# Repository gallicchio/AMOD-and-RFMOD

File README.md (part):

# AMOD and RF-MOD: boards of analog and RF building blocks

Nine 100 x 100 mm boards of "tiles" for an FPGA with fast converters: seven first-level boards (for the ECP5-2ADC-2DAC
board, or an Icepi Zero with its AD9280/AD9708 module), among them AMOD-N, as simple as the first, the conversion board
AMOD-C and two motor boards, AMOD-M (brushed motors and actuators) and AMOD-B (a brushless gimbal motor), and two
second-level boards built around the ECP5-2ADC-2DAC board's two DACs and two ADCs: PhMOD (AMOD-2 until Prompt 17) and
IQ-MOD.  Each tile is one circuit with its own SMA jacks: cable a DAC to its input and its
output to an ADC, and compare the measurement with the expected result printed beside it.  The silkscreen draws every
tile's wiring as it is laid in copper.  The tutorial they serve is `icepi-zero-dac-adc/tutorial/`, whose Appendix D
specified them.

Rev A, 2026-10-25 (AMOD-N, AMOD-C, AMOD-M and AMOD-B added 2026-10-28).  Designed by Claude with Jason Gallicchio, not yet ordered.

| board | what | tiles | layers | parts per board |
|---|---|---|---|---|
| [AMOD-P](docs/HANDBOOK_amod_p.md) | passive: pads, RC and LC filters, resonators, a crystal, a clipper, a delay line, LEDs, an AM loopstick | 13 | 2 | $17.07 |
| [AMOD-N](docs/HANDBOOK_amod_n.md) | the second passive board: calibration standards, two splitters, a quarter-wave stub, a low-pass, a diode detector, a bias-T, a 1:1 balun and a 1:4 transformer; a step attenuator (by hand or the FPGA) and an oscillator on the Pmod's 3.3 V | 11 | 4 | $43.91 |
| [AMOD-A](docs/HANDBOOK_amod_a.md) | active on USB-C: gain blocks, an HF LNA, an HB100 Doppler radar, a one-pin ADC, a 4046 PLL, heat, a mixer, impedance and I-V, ultrasound, audio | 12 | 4 | $49.73 |
| [AMOD-C](docs/HANDBOOK_amod_c.md) | conversion: two regulators and an electronic load, a charge pump, switched capacitors (a filter, a resistor), a delta-sigma modulator, a track-and-hold, a SAR comparator, a differential pair, a cascode, a V-to-F, a precision rectifier | 12 | 4 | $43.93 |
| [AMOD-M](docs/HANDBOOK_amod_m.md) | motors on a 5-16 V supply: a DC motor with its encoder, a stepper, a servo, a solenoid's flyback three ways, a DC-coupled bridge amplifier, a buck power stage, and a hall, an optical and a load-cell sensor for their loops | 11 | 4 | $36.49 |
| [AMOD-B](docs/HANDBOOK_amod_b.md) | a brushless gimbal motor on a 5-12 V supply: a three-phase driver from the FPGA, the motor over a magnetic encoder, two halls and an index sensor, its back-EMF, its phase and bus currents, its vibration, and an IMU | 12 | 4 | $42.45 |
| [RF-MOD](docs/HANDBOOK_rf_mod.md) | 915 MHz and 2.4 GHz: a diode-ring mixer, two filters, a QPL9547 LNA, a gain block, two ADL5350 mixers, a synthesizer with two outputs, a TRF3722 I/Q transmitter, power and a 25 MHz reference | 10 | 4 | $66.51 |
| [PhMOD](docs/HANDBOOK_phmod.md) | physics at HF, magnetic resonance, the ionosphere and light: a 1 W pulse amplifier and duplexer, a two-channel HF receiver, a VLF loop amplifier, a reflection bridge, coupled resonators, a coil driver, a noise source, a laser driver with an RF bias-T | 10 | 4 | $77.89 |
| [IQ-MOD](docs/HANDBOOK_iq_mod.md) | coherent I/Q and microwave physics, 0.4-6 GHz: an I/Q modulator and demodulator on one synthesizer's two outputs, a dual directional coupler, an LNA, a log detector, a switch, a noise source, GNSS, an ODMR loop | 11 | 4 | $99.71 |
| [Icepi adapter](icepi_adapter/README.md) | the tutorial's 2x12 Icepi Zero adapter with a Pmod socket | | 4 | hand-soldered |

Each tile's name and what it does are printed on the board: the jacks' names sit on their own tile's frame beside each
jack, a tile's title in words on its top frame where it fits, its ranges and levels inside it.  Ports are named in
capitals (IN, OUT, LO), tiles in mixed case (Step attenuator, Diode mixer), everything else in lower case.  Turn a board
over and each tile has a panel on the back under it: its limits, its loads, its supply, and where there is room a small
plot of the response to expect, so the board can be cabled without the handbook open.  Below, each board's
picture and a table of its tiles, each row a summary of the tile's entry in the board's handbook (linked from the tile's
number), where the tile has its own picture, what to expect, the circuit and its parts.  What to buy beside the boards,
with links and prices, is in [docs/KIT.md](docs/KIT.md).

## The boards

<!-- board:amod_p -->
### [AMOD-P](docs/HANDBOOK_amod_p.md): the passive board

| tile | what it does | chip | specs | limits | experiments | how to use it | you need |
|---|---|---|---|---|---|---|---|
| [**p1**](docs/HANDBOOK_amod_p.md#p1) pi pad | Divides the voltage by 10 (-20 dB) and looks like 50 ohm from both ports. | passive | 61.9 / 249 / 61.9 ohm pi; -20.0 dB; DC to well past 30 MHz. | -20 dB only between 50 ohm on both sides (-14 dB into a high impedance); about 0.1 W (+-3 V) at IN. | A known weak signal for a receiver or LNA; padding a mismatched cable; checking the ADC's 50 ohm setting. | DAC to IN, OUT to the ADC set to 50 ohm. | Nothing beyond SMA cables. |
| [**p2**](docs/HANDBOOK_amod_p.md#p2) RC low-pass | A first-order RC low-pass: passes below 159 kHz and falls 20 dB per decade above. | passive | 1 k and 1 nF; -3 dB at 159 kHz; time constant 1 us. | OUT is a 1 k source: read it on the ADC's high-impedance setting (50 ohm divides it by 21). | A Bode plot, 45 degrees at the corner, the step response, the lag plant for feedback control. | DAC to IN, OUT to the ADC on high impedance; sweep the frequency or send a step. | Nothing beyond SMA cables. |
| [**p3**](docs/HANDBOOK_amod_p.md#p3) RC high-pass | A first-order RC high-pass, the mirror image of p2. | passive | 1 nF and 1 k; -3 dB at 159 kHz; +20 dB per decade below. | OUT is a 1 k source: read it on high impedance. | A Bode plot, AC coupling, a differentiator (a step gives a 1 us spike). | DAC to IN, OUT to the ADC on high impedance. | Nothing beyond SMA cables. |
| [**p4**](docs/HANDBOOK_amod_p.md#p4) series RLC | A series 100 uH and 220 pF resonator between 50 ohm ports: a band-pass peak that the DIP switch moves. | passive | 1.07 MHz with both switches off, 0.98 (way 1, +47 pF), 0.89 (way 2, +100 pF), 0.83 (both); Q about 6. | The 50 ohm ports load it: Q is 6, where the coil alone would allow about 60. | Resonance and Q, the phase through resonance, tracking a resonance with a lock-in or a PLL, a resonant plant to control. | Sweep the DAC into IN, OUT to the ADC (50 ohm); set the DIP switch. | Nothing beyond SMA cables. |
| [**p5**](docs/HANDBOOK_amod_p.md#p5) LC low-pass | A 5th-order Butterworth LC low-pass at 9 MHz: the anti-alias filter for a 25 MS/s ADC, or the smoothing filter after a DAC. | passive | -3 dB at 8.9 MHz, -30 dB at 18 MHz; 50 ohm in and out. | The response is as designed only with 50 ohm on both ports. | Aliasing with and without it; a filter's magnitude, phase and group delay; cleaning a DAC's staircase. | Between the DAC and its load, or between a signal and the ADC (50 ohm). | Nothing beyond SMA cables. |
| [**p6**](docs/HANDBOOK_amod_p.md#p6) LC low-pass | A 3rd-order LC low-pass near 120 kHz: turns a one-bit (delta-sigma or PWM) stream into a tone. | passive | 10 nF, 150 uH, 10 nF (C0G); -3 dB at 118 kHz; 50 ohm. | Designed for 50 ohm on both ports. | One-bit DAC reconstruction, delta-sigma noise shaping seen at the output, a slow plant for control. | DAC (or a one-bit stream through 50 ohm) to IN, OUT to the ADC. | Nothing beyond SMA cables. |
| [**p7**](docs/HANDBOOK_amod_p.md#p7) band-pass | A 3rd-order LC band-pass, 4.7-7.5 MHz: the band round the tutorial's 6.25 MHz digital-communications carrier. | passive | Peak at 6.3 MHz, -3 dB from 4.7 to 7.5 MHz; 50 ohm. | Only 3rd order: the skirts fall about 18 dB per octave. | Band-limiting a modem's chips (spread spectrum, LoRa chirps); a transmitter's harmonics removed; a receiver's front end. | In line between the DAC and the ADC, or ahead of a receiver. | Nothing beyond SMA cables. |
| [**p8**](docs/HANDBOOK_amod_p.md#p8) quartz crystal | A 4 MHz quartz crystal in series between the jacks: a very sharp pass at its series resonance and a notch at its parallel resonance about 6 kHz above. | passive | f_s near 4.000 MHz (-3.7 dB); f_p about 6 kHz higher; Q about 50,000 (C_m 15 fF, C_0 4 pF). | Needs frequency steps of a few hertz (the FPGA's NCO); keep the drive under about +-1 V (crystals have a drive-level limit near 100 uW). | Q from the width and from the ring-down; series against parallel resonance; pulling f_p with a capacitor across OUT (an SMA tee); the temperature coefficient. | Sweep the DAC slowly through 4.000 MHz into IN, OUT to the ADC, lock-in detection in the gateware. | An SMA tee and a few capacitors (or open cable stubs) for the pulling experiment. |
| [**p9**](docs/HANDBOOK_amod_p.md#p9) ceramic res. | A 455 kHz ceramic resonator in series: a pass at 455 kHz and a notch a few kHz above; the AM superhet's IF element. | passive | Q of a few hundred: between p4's LC (6) and p8's quartz (50,000). | A two-terminal resonator, not a three-terminal IF filter: one peak, no flat passband. | Q compared across LC, ceramic and quartz; an IF stage for a superhet built in gateware. | Sweep 440-480 kHz into IN, OUT to the ADC. | Nothing beyond SMA cables. |
| [**p10**](docs/HANDBOOK_amod_p.md#p10) clipper | 1 k in series and a 1N4148 diode each way to ground: clips any signal to about +-0.6 V. | passive | Clips at +-0.6 V; a 1 k source. | Read OUT on high impedance; up to +-4 V in (the 1 k holds the diode current to 4 mA). | Harmonics of a clipped sine against amplitude; odd harmonics, and even ones with a DC offset added; distortion. | DAC sine to IN, OUT to the ADC on high impedance, FFT in the gateware or Python. | Nothing beyond SMA cables. |
| [**p11**](docs/HANDBOOK_amod_p.md#p11) delay line | A 400 ns, 50 ohm delay line made of 20 LC sections, with taps every 100 ns: 260 feet of RG-58 on a board. | passive | Z0 51 ohm, 20 ns a section, cut-off 16 MHz, flat to about 10 MHz; taps through 470 ohm. | Disperses near 16 MHz (a chirp spreads); a tap is x1 into a high impedance, /10 into 50 ohm. | Reflections from an open, a short and a matched end; time-domain reflectometry; echoes for an equalizer; a radar target on a cable; a pure-delay plant for control. | A pulse or chirp from the DAC into IN; OUT open, shorted or terminated; the taps and OUT to the ADCs. | An SMA short and a 50 ohm terminator (the kit's ANNE-50+) for the reflection experiments. |
| [**p12**](docs/HANDBOOK_amod_p.md#p12) LEDs | Four LEDs (red, yellow, green, blue) behind 100 ohm, one at a time from the DIP switch: Planck's constant from the voltage where each starts to glow. | passive | 630, 596, 525 and 469 nm (DIP ways 1-4); 100 ohm in series; IN 0-5 V. | The InGaN green and blue sit above the line (their knee is not just hc / e lambda); the colours are not printed, so light them. | Planck's constant; LED I-V curves (with AMOD-A's a10); light against current. | Ramp the DAC (or the host's LED output) into IN and read the LED loop's voltage; one DIP way at a time. | Nothing (a dark room helps). |
| [**p13**](docs/HANDBOOK_amod_p.md#p13) AM loopstick | An AM-band antenna: a ferrite-rod coil screwed into the terminal, tuned by four switched capacitors or an external tuning capacitor on VAR C, its tap on the jack. | passive | With a 330 uH coil: 1.28 MHz (47 pF) down to 0.40 MHz (470 pF), and the sums between; the kit's 240 uH coil tunes about 17 % higher. | The switches tune in 15 steps; continuous tuning needs a capacitor on VAR C (a polyvaricon and its dial are 20 mm square: no room on the tile).  A weak signal that needs a4's gain before the ADC. | Real AM stations; the resonance and Q of a loopstick; the tutorial's AM radio gateware. | Coil ends to GND and HOT, its tap (if it has one) to TAP; rod along the bottom edge with two cable ties; OUT to AMOD-A's a4, a4 to the ADC; the DIP picks the band, or a tuning capacitor on VAR C (frame to GND) tunes within it. | An AM loopstick coil and two cable ties (kit: Atomic-29 240 uH loopstick, Panduit PLT1M-C); optionally a 365 pF tuning capacitor with a knob (kit: Amplified Parts single-section 365 pF). |

More on each tile, with its picture, in the [AMOD-P handbook](docs/HANDBOOK_amod_p.md); what to buy in [KIT.md](docs/KIT.md).

<!-- /board:amod_p -->

<!-- board:amod_n -->
### [AMOD-N](docs/HANDBOOK_amod_n.md): the second passive board

| tile | what it does | chip | specs | limits | experiments | how to use it | you need |
|---|---|---|---|---|---|---|---|
| [**n1**](docs/HANDBOOK_amod_n.md#n1) calibration | Calibration standards for a network analyzer, on the board: a short and an open at the jacks' pins, a 50 ohm load, a 25 ohm check standard and a thru. | passive | SHORT: the centre pin poured to ground all round.  OPEN: the bare pin.  LOAD: 2 x 100 ohm at the end of 4 mm of 50 ohm line.  25 OHM: 2 x 49.9 ohm (VSWR 2, \|Gamma\| 1/3, 9.5 dB return loss).  THRU: 19.8 mm of 50 ohm coplanar line, about 115 ps. | The standards are modelled, not measured: the open's fringing (tens of fF) and the short's inductance (tens of pH) count above about 3 GHz, and the 0402 load is a 20 dB return loss at 3 GHz.  Check them once against the NanoVNA's SMA standards. | A full SOLT calibration of IQ-MOD's reflectometer (q1, q2, q5) or of a NanoVNA at the board's surface; the 25 ohm standard as its check; every other tile then measured from its pads with its jacks taken out (they are all the same part). | The analyzer's port to SHORT, OPEN and LOAD in turn; its two ports to THRU A and THRU B for the two-port step; then any tile. | Nothing beyond SMA cables. |
| [**n2**](docs/HANDBOOK_amod_n.md#n2) resistive splitter | A resistive power splitter: three 16.9 ohm in a star, every port 50 ohm, 6 dB from any port to either other, from DC to 6 GHz. | passive | 3 x 16.9 ohm (50 / 3); -6.0 dB each way; DC-6 GHz; OUT 1 and OUT 2 on lines of equal length. | No isolation (OUT 1 to OUT 2 is also -6 dB); 6 dB of loss where a transformer splitter loses 3; about +20 dBm at IN (1/16 W resistors). | One DAC into both ADCs to measure the converters' own gain and skew; the reference and test paths of a scalar network analyzer; its isolation against n3's. | IN from the source; OUT 1 and OUT 2 to two 50 ohm loads.  Symmetric: any port can be IN. | Nothing beyond SMA cables. |
| [**n3**](docs/HANDBOOK_amod_n.md#n3) transformer splitter | A transformer power splitter (and combiner): half the power to each port, 3 dB, with the two ports isolated from each other, 0.5-400 MHz. | [ADP-2-1+](https://www.minicircuits.com/WebStore/dashboard.html?model=ADP-2-1%2B) | 3.1-3.4 dB from SUM to each port; 25-34 dB between port 1 and port 2; 0.5-400 MHz (the datasheet). | A transformer: nothing below 0.5 MHz; the isolation holds only with 50 ohm on all three ports; pins 2 and 5 are joined and must not be grounded. | Two DACs combined into one amplifier for a two-tone intermodulation test (AMOD-A's a4, PhMOD's h5); one reference split to two boards; isolation measured against n2's. | SUM from the source (or to the load when combining); PORT 1 and PORT 2 to two loads (or from two sources). | Nothing beyond SMA cables. |
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
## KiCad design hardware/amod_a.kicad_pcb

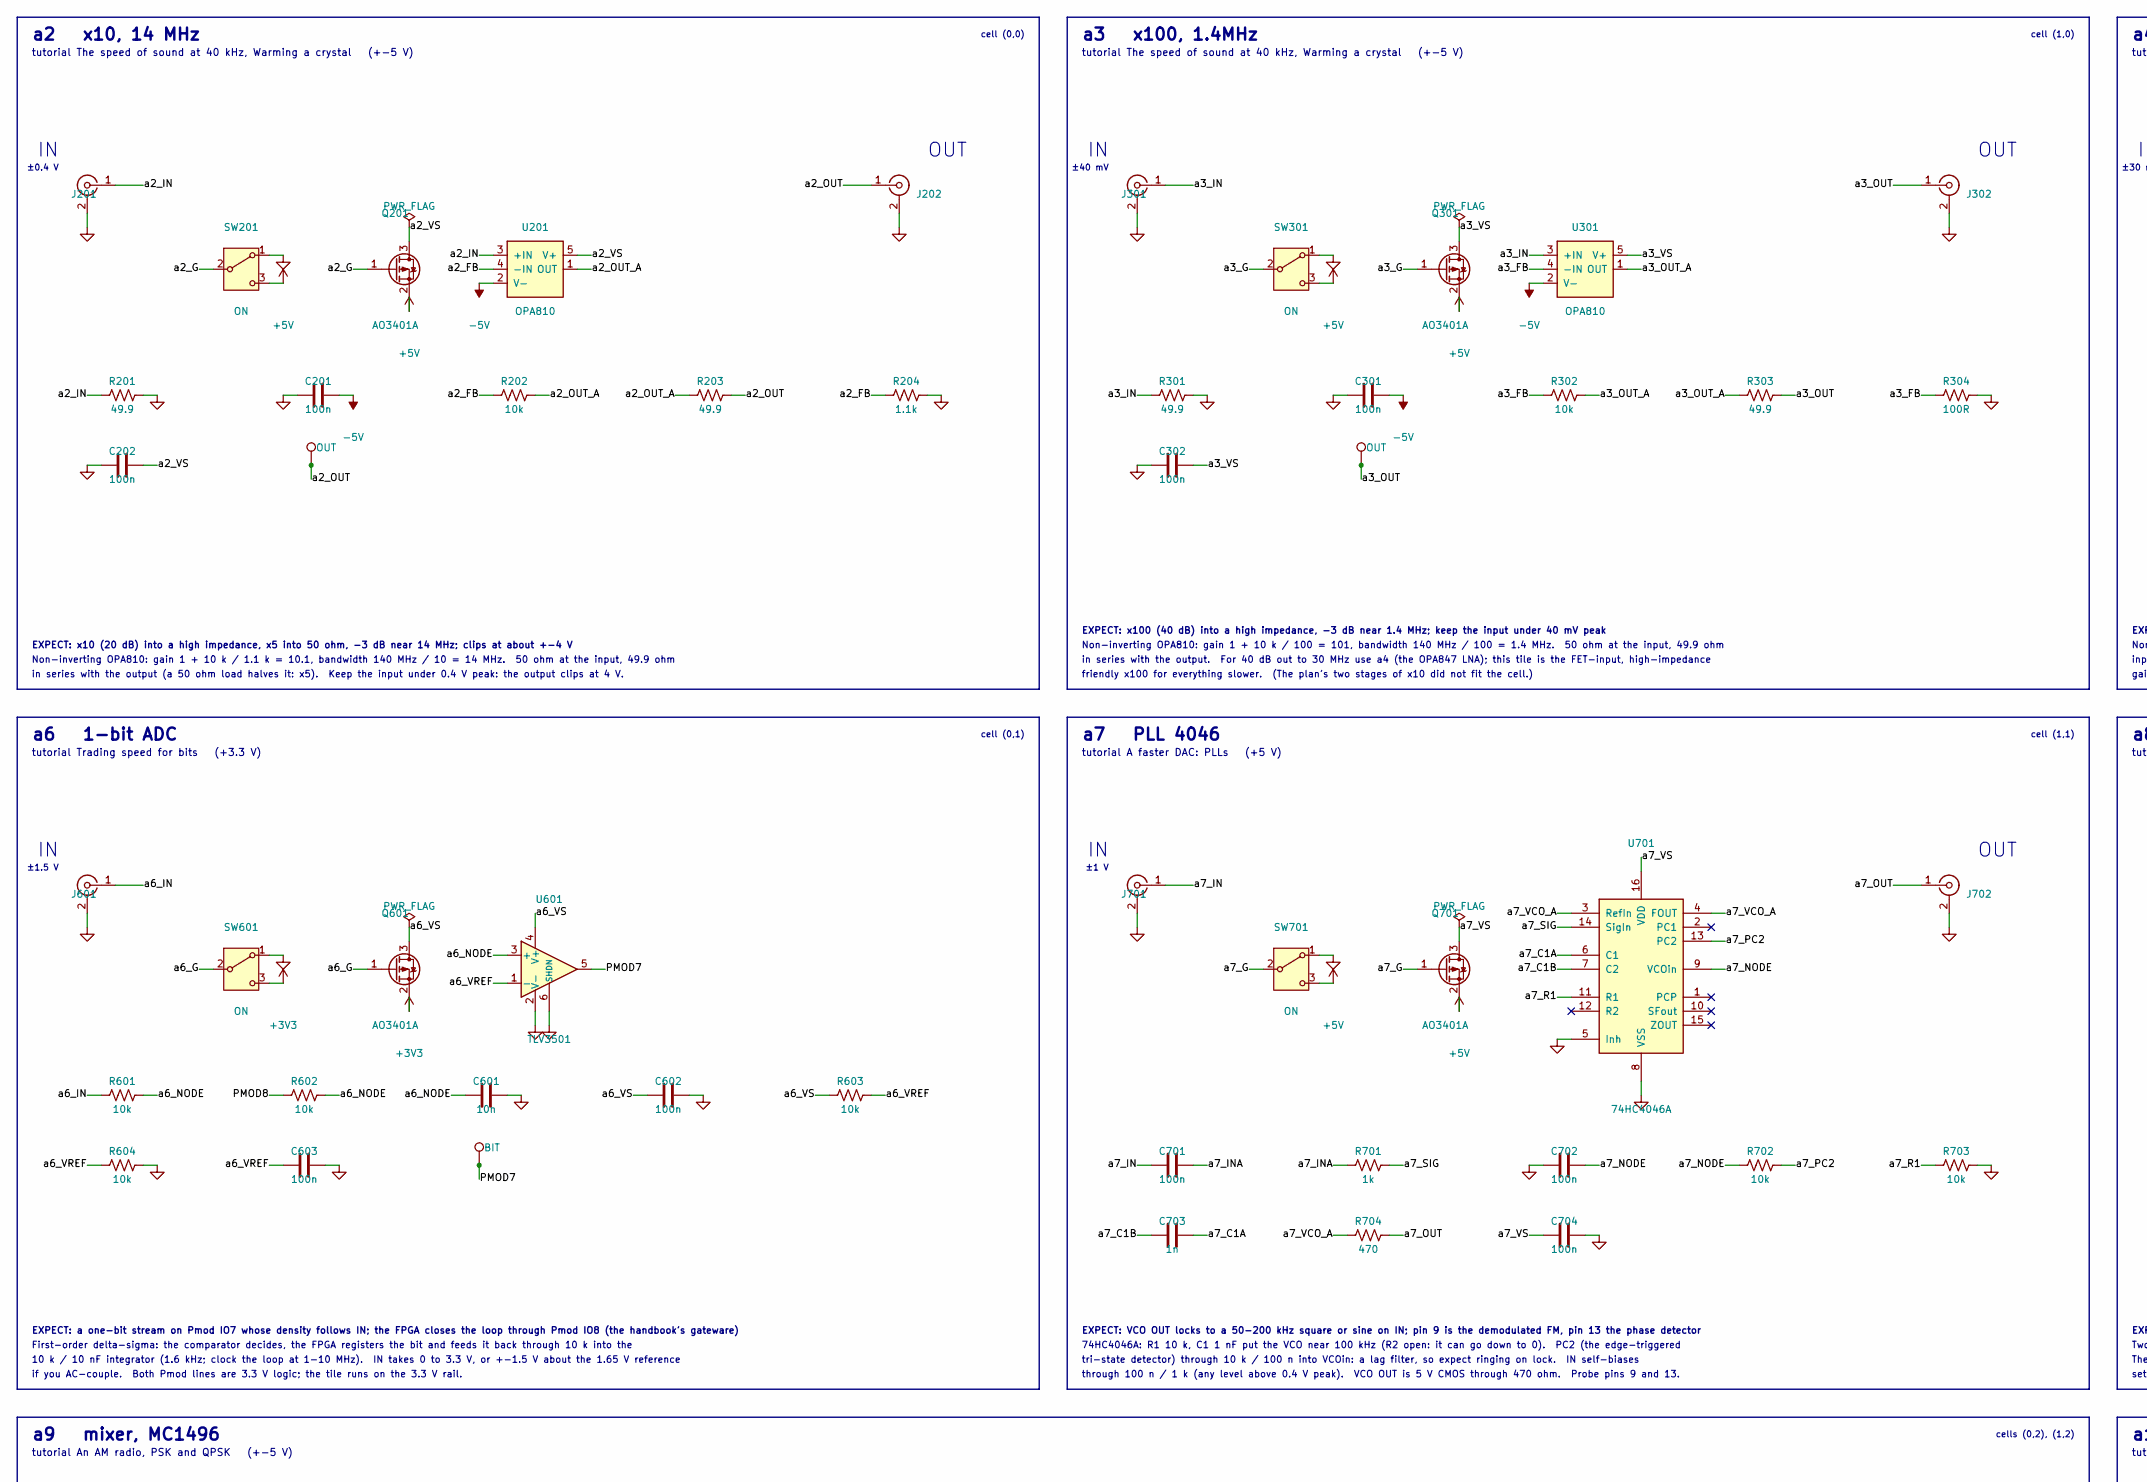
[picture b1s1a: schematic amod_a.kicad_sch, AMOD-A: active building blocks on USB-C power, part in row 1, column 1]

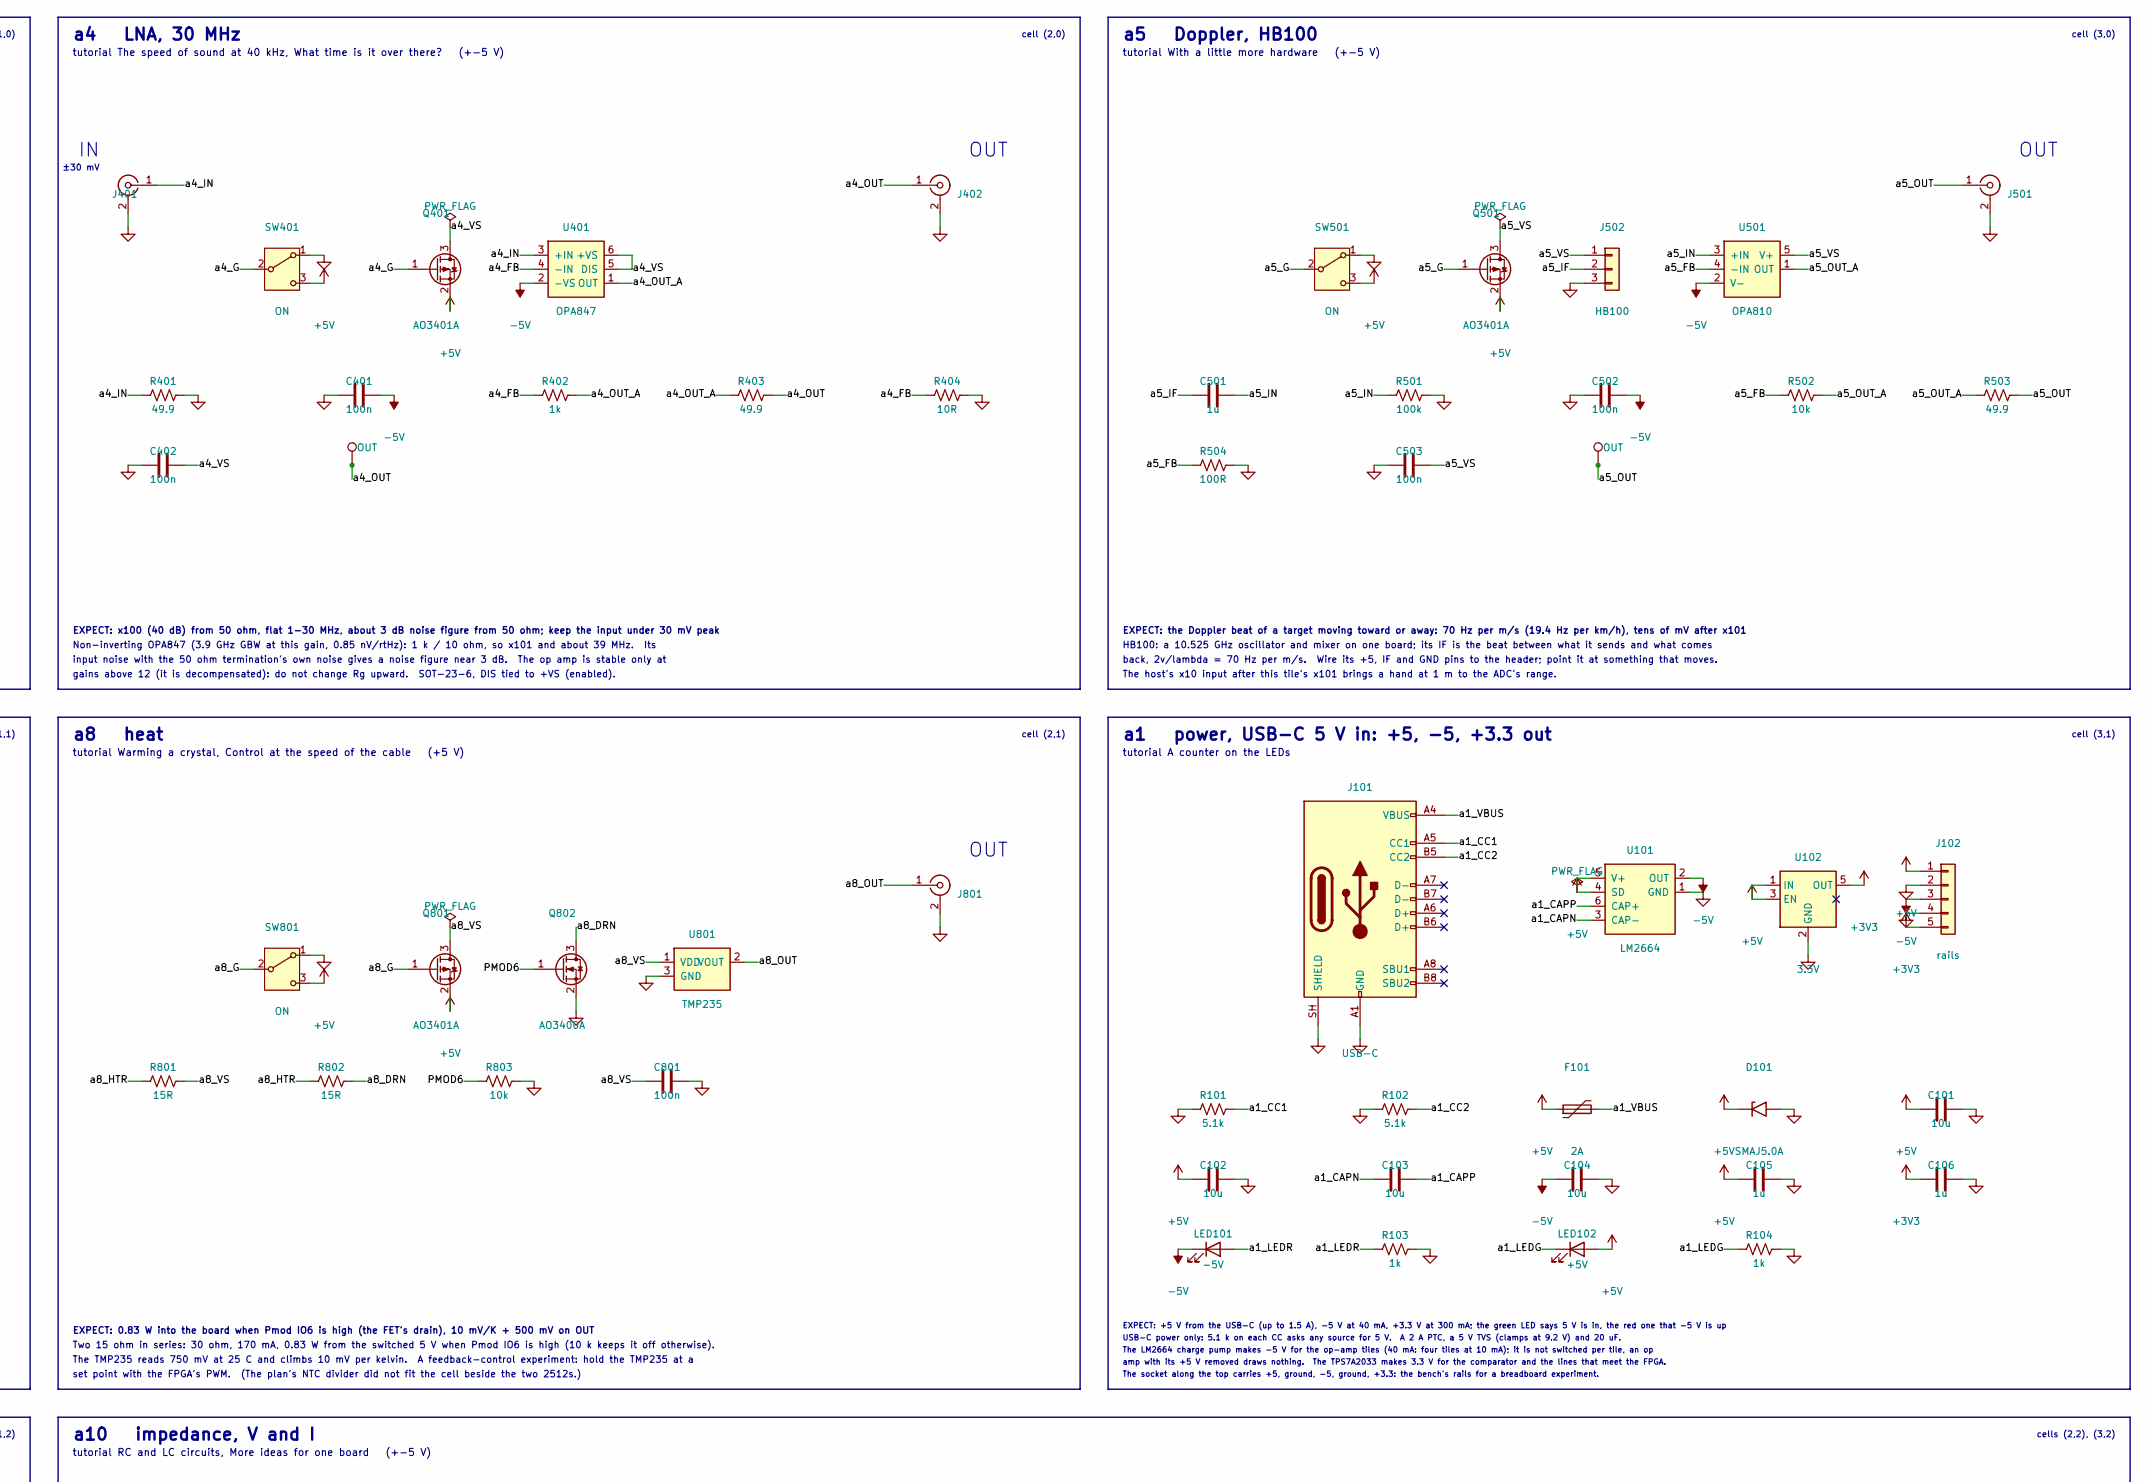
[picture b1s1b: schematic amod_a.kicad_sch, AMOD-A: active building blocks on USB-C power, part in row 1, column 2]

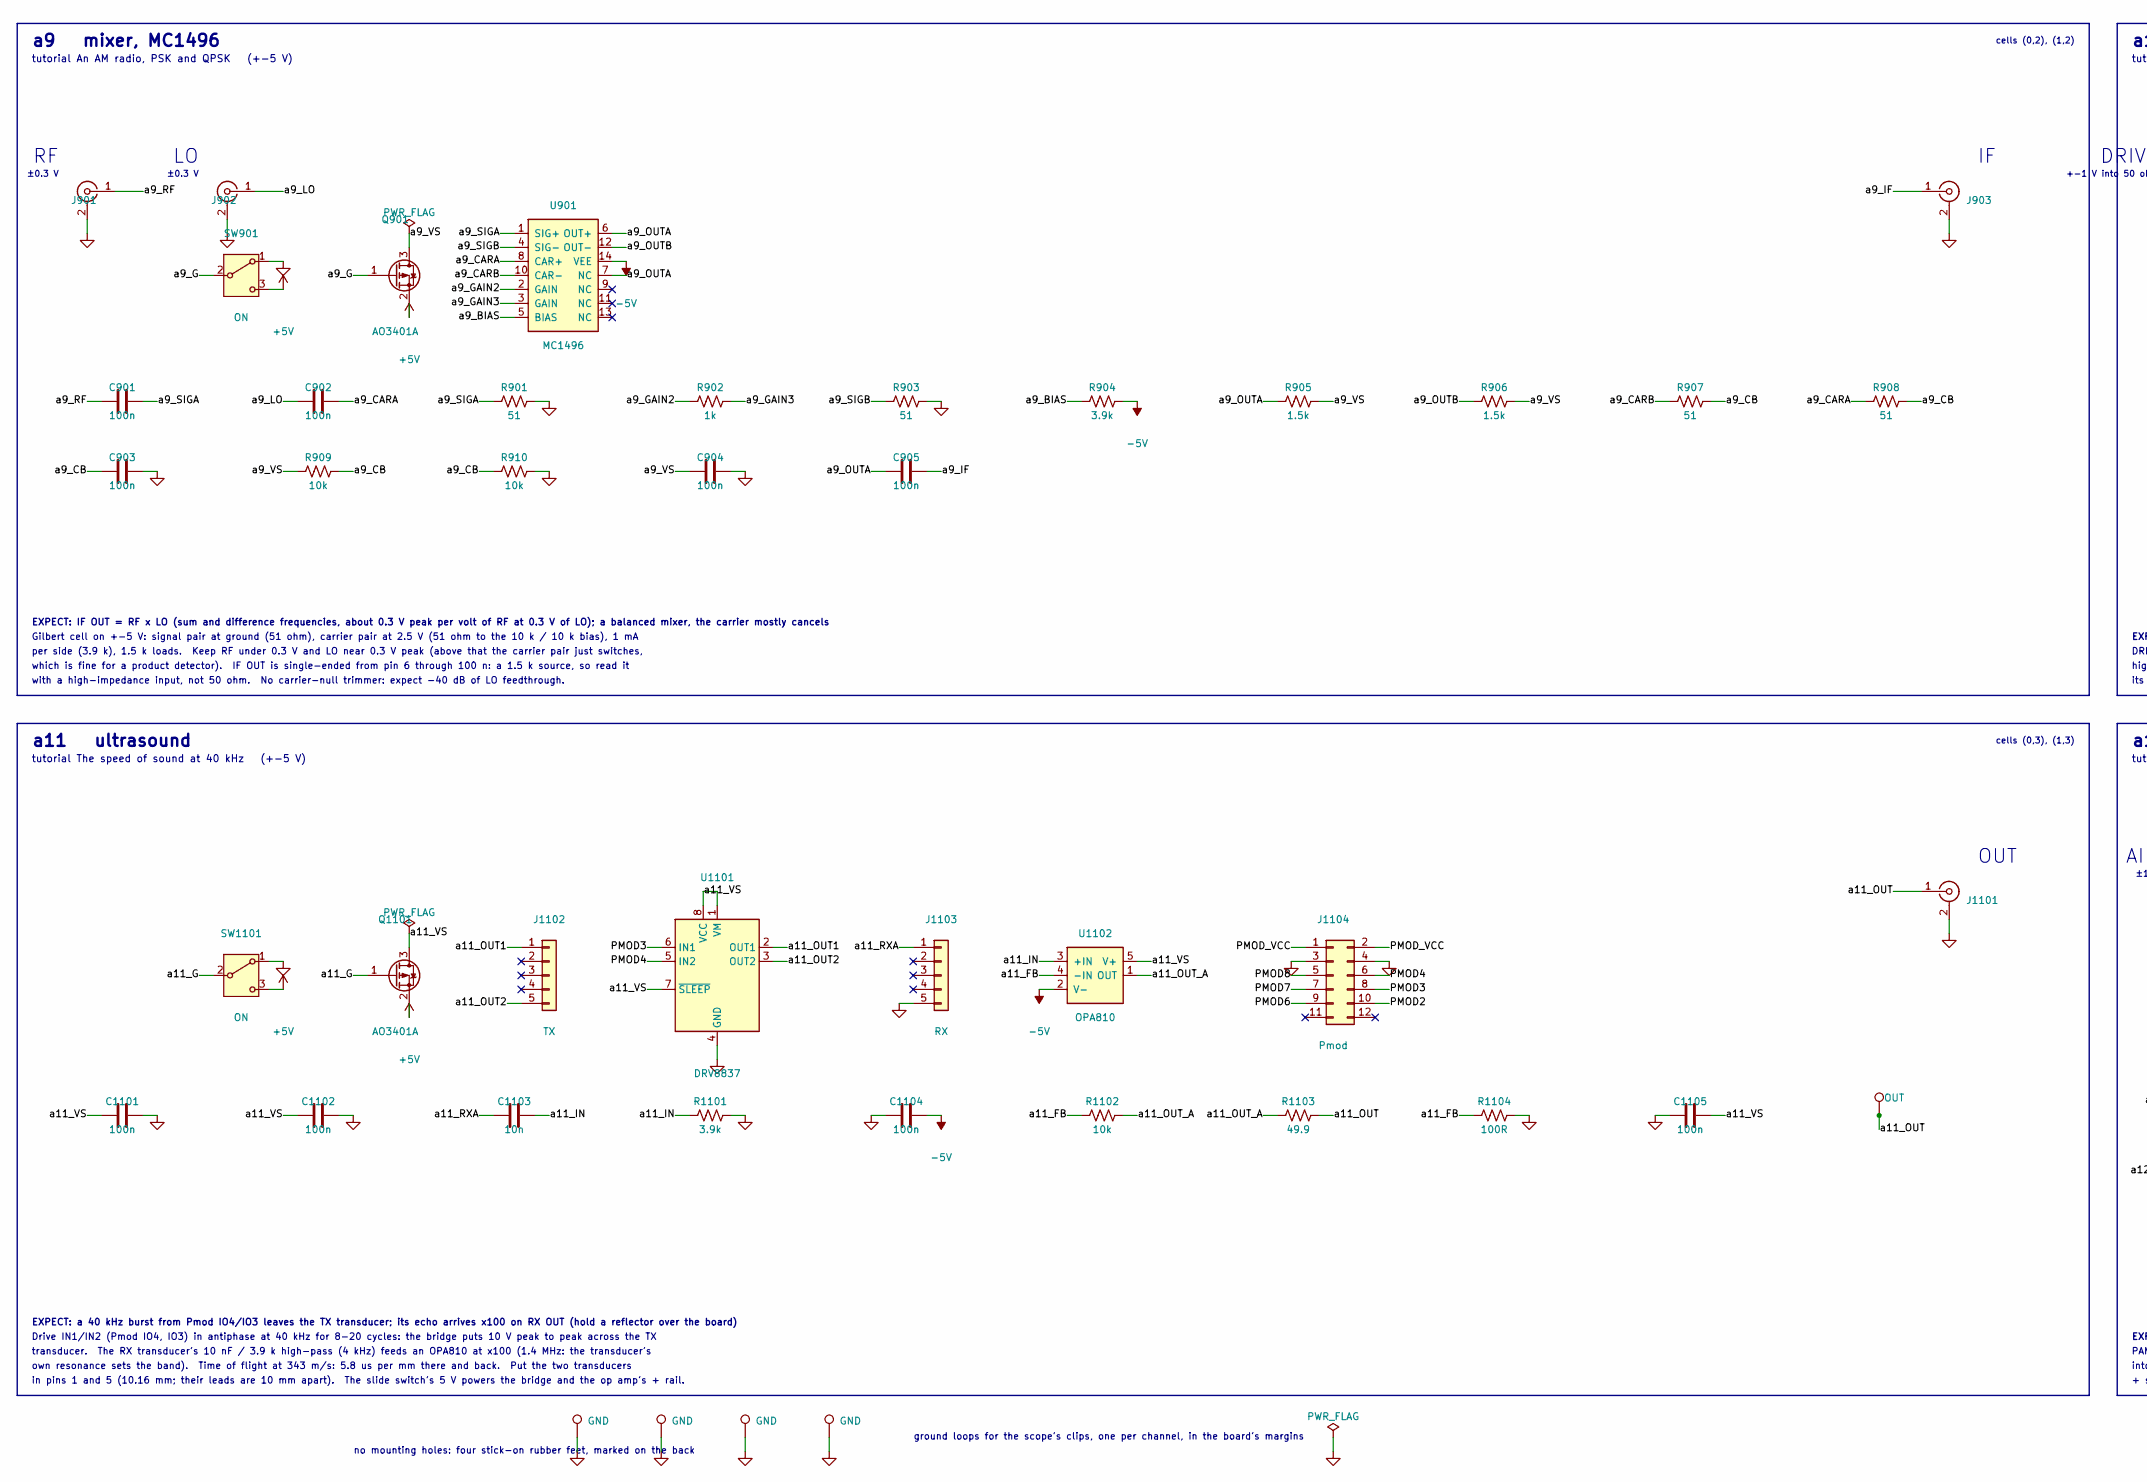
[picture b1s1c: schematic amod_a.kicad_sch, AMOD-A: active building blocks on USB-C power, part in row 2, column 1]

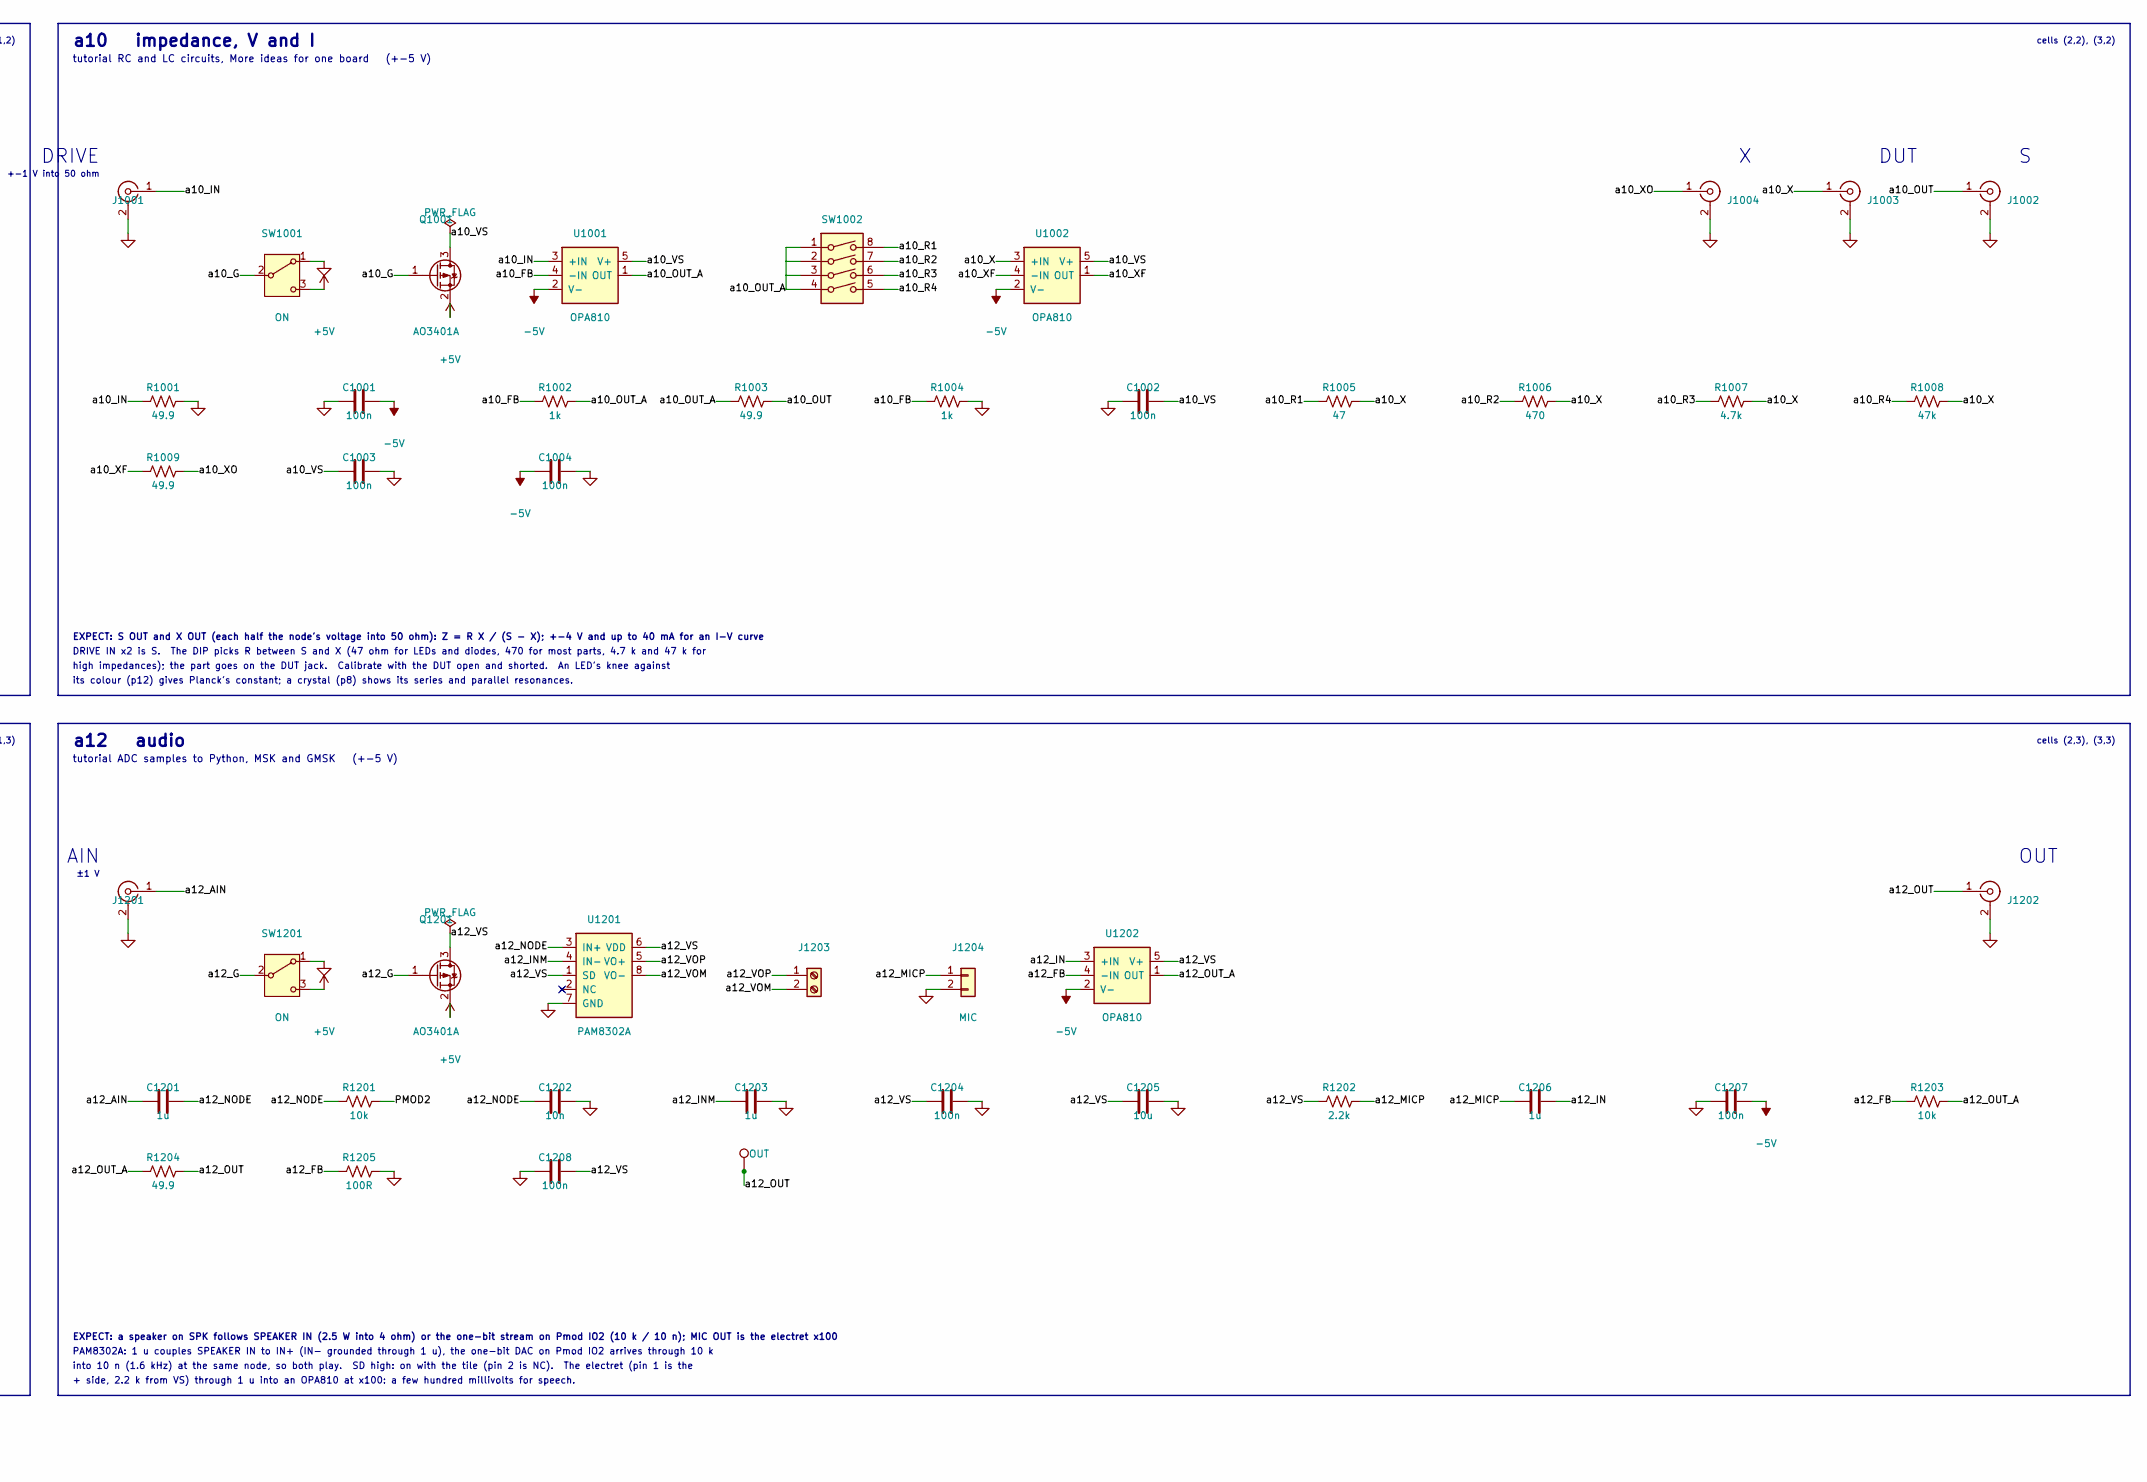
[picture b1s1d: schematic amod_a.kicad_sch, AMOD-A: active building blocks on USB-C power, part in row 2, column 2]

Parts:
C101, C102, C103, C104, C1205: 10u; C_0805_2012Metric; MPN CL21A106KAYNNNE; LCSC C15850
C105, C106, C501, C1201: 1u; C_0805_2012Metric; MPN CL21B105KBFNNNE; LCSC C28323
C201, C202, C301, C302, C401, C402, C502, C503, C801, C901, C902, C903, C904, C905, C1001, C1002, C1003, C1004, C1101, C1102, C1104, C1105, C1204, C1207, C1208: 100n; C_0603_1608Metric; MPN CC0603KRX7R9BB104; LCSC C14663
C601, C1103, C1202: 10n; C_0805_2012Metric; MPN 0805CG103J500NT; LCSC C2971995
C602, C603: 100n; C_0805_2012Metric; MPN CC0805KRX7R9BB104; LCSC C49678
C701, C702, C704: 100n; C_0402_1005Metric; MPN CL05B104KO5NNNC; LCSC C1525
C703: 1n; C_0402_1005Metric; MPN 0402B102K500NT; LCSC C1523
C1203, C1206: 1u; C_0603_1608Metric; MPN CL10A105KB8NNNC; LCSC C15849
D101: SMAJ5.0A; D_SMA; MPN SMAJ5.0A; LCSC C78401
F101: 2A; Fuse_1812_4532Metric; MPN MF-MSMF200-2; LCSC C210837
J101: USB-C; USB_C_Receptacle_HRO_TYPE-C-31-M-12; MPN TYPE-C-31-M-12; LCSC C165948
J102: rails; PinSocket_1x05_P2.54mm_Vertical; MPN PZ254-1-05-Z-8.5; LCSC C2894928
J201, J202, J301, J302, J401, J402, J501, J601, J701, J702, J801, J901, J902, J903, J1001, J1002, J1003, J1004, J1101, J1201, J1202: SMA; SMA_BWSMA-KE-Z001_Vertical; MPN BWSMA-KE-Z001; LCSC C496549
J502: HB100; PinHeader_1x03_P2.54mm_Vertical; MPN PZ254V-11-03P; LCSC C2937625
J1102: TX; PinSocket_1x05_P2.54mm_Vertical; MPN PZ254-1-05-Z-8.5; LCSC C2894928
J1103: RX; PinSocket_1x05_P2.54mm_Vertical; MPN PZ254-1-05-Z-8.5; LCSC C2894928
J1104: Pmod; PinHeader_2x06_P2.54mm_Horizontal_PZ254R-12-12P; MPN PZ254R-12-12P; LCSC C492434
J1203: SPK; TerminalBlock_KF301_1x02_P5.00mm; MPN KF301-5.0-2P; LCSC C474881
J1204: MIC; PinSocket_1x02_P2.54mm_Vertical; MPN PZ254-1-02-Z-8.5; LCSC C2894925
LED101: -5V; LED_0805_2012Metric_Kbar; MPN NCD0805R1; LCSC C84256
LED102: +5V; LED_0805_2012Metric_Kbar; MPN KT-0805G; LCSC C2297
Q201, Q301, Q401, Q501, Q601, Q701, Q801, Q901, Q1001, Q1101, Q1201: AO3401A; SOT-23; MPN AO3401A; LCSC C15127
Q802: AO3400A; SOT-23; MPN AO3400A; LCSC C20917
R101, R102: 5.1k; R_0805_2012Metric; MPN 0805W8F5101T5E; LCSC C27834
R103, R104: 1k; R_0805_2012Metric; MPN 0805W8F1001T5E; LCSC C17513
R201, R203, R301, R303, R401, R403, R503, R1001, R1003, R1009, R1103, R1204: 49.9; R_0603_1608Metric; MPN SR0603FR-7T49R9L; LCSC C6230117
R202, R302, R502, R602, R803, R909, R910, R1102, R1201, R1203: 10k; R_0603_1608Metric; MPN 0603WAF1002T5E; LCSC C25804
R204: 1.1k; R_0603_1608Metric; MPN 0603WAF1101T5E; LCSC C22764
R304, R504, R1104, R1205: 100R; R_0603_1608Metric; MPN 0603WAF1000T5E; LCSC C22775
R402, R1002, R1004: 1k; R_0603_1608Metric; MPN 0603WAF1001T5E; LCSC C21190
R404: 10R; R_0603_1608Metric; MPN 0603WAF100JT5E; LCSC C22859
R501: 100k; R_0402_1005Metric; MPN 0402WGF1003TCE; LCSC C25741
R601, R603, R604: 10k; R_0805_2012Metric; MPN 0805W8F1002T5E; LCSC C17414
R701, R902: 1k; R_0402_1005Metric; MPN 0402WGF1001TCE; LCSC C11702
R702, R703: 10k; R_0402_1005Metric; MPN 0402WGF1002TCE; LCSC C25744
R704, R1006: 470; R_0402_1005Metric; MPN 0402WGF4700TCE; LCSC C25117
R801, R802: 15R; R_2512_6332Metric; MPN 25121WF150JT4E; LCSC C20087
R901, R903, R907, R908: 51; R_0402_1005Metric; MPN 0402WGF510JTCE; LCSC C25125
R904: 3.9k; R_0402_1005Metric; MPN 0402WGF3901TCE; LCSC C51721
R905: 1.5k; R_0402_1005Metric; MPN 0402WGF1501TCE; LCSC C25867
R906: 1.5k; R_0805_2012Metric; MPN 0805W8F1501T5E; LCSC C4310
R1005: 47; R_0402_1005Metric; MPN 0402WGF470JTCE; LCSC C25118
R1007: 4.7k; R_0402_1005Metric; MPN 0402WGF4701TCE; LCSC C25900
R1008: 47k; R_0402_1005Metric; MPN 0402WGF4702TCE; LCSC C25792
R1101: 3.9k; R_0805_2012Metric; MPN 0805W8F3901T5E; LCSC C17614
R1202: 2.2k; R_0805_2012Metric; MPN 0805W8F2201T5E; LCSC C17520
SW201, SW301, SW401, SW501, SW601, SW701, SW801, SW901, SW1001, SW1101, SW1201: ON; SW_SPDT_Shouhan_MSK12C02; MPN MSK12C02; LCSC C431540
SW1002: DIP4; SW_DIP_SPSTx04_Slide_1.27mm_DSHP04; MPN DSHP04TSGET; LCSC C40736
TP201, TP301, TP401, TP501, TP1101, TP1201: OUT; TestPoint_Loop_RH-5019; MPN RH-5019; LCSC C5199800
TP601: BIT; TestPoint_Loop_RH-5019; MPN RH-5019; LCSC C5199800
TP9901, TP9902, TP9903, TP9904: GND; TestPoint_Loop_RH-5019; MPN RH-5019; LCSC C5199800
U101: LM2664; SOT-23-6; MPN LM2664M6X/NOPB; LCSC C108573
U102: 3.3V; SOT-23-5; MPN TPS7A2033PDBVR; LCSC C2862740
U201, U301, U501, U1001, U1002, U1102, U1202: OPA810; SOT-23-5; MPN OPA810IDBVR; LCSC C2833513
U401: OPA847; SOT-23-6; MPN OPA847IDBVT; LCSC C2059024
U601: TLV3501; SOT-23-6; MPN TLV3501AIDBVR; LCSC C193413
U701: 74HC4046A; TSSOP-16_4.4x5mm_P0.65mm; MPN 74HC4046APW-Q100J; LCSC C546981
U801: TMP235; SOT-23; MPN TMP235A4DBZR; LCSC C2868809
U901: MC1496; SOIC-14_3.9x8.7mm_P1.27mm; MPN MC1496DR2G; LCSC C7295
U1101: DRV8837; Texas_DSG0008A_WSON-8-1EP_2x2mm_P0.5mm_EP0.9x1.6mm; MPN DRV8837DSGR; LCSC C39159
U1201: PAM8302A; MSOP-8_3x3mm_P0.65mm; MPN PAM8302AASCR; LCSC C113367

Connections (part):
+3V3: C106.1, J102.5, Q601.2 (S), SW601.3 (C), U102.5 (OUT)
+5V: C101.1, C102.1, C105.1, D101.1 (A1), F101.1, J102.1, LED102.2 (A), Q201.2 (S), Q301.2 (S), Q401.2 (S), Q501.2 (S), Q701.2 (S), Q801.2 (S), Q901.2 (S), Q1001.2 (S), Q1101.2 (S), Q1201.2 (S), SW201.3 (C), SW301.3 (C), SW401.3 (C), SW501.3 (C), SW701.3 (C), SW801.3 (C), SW901.3 (C), SW1001.3 (C), SW1101.3 (C), SW1201.3 (C), U101.4 (SD), U101.5 (V+), U102.1 (IN), U102.3 (EN)
-5V: C104.1, C201.2, C301.2, C401.2, C502.2, C1001.2, C1004.1, C1104.2, C1207.2, J102.3, LED101.1 (K), R904.2, U101.2 (OUT), U201.2 (V-), U301.2 (V-), U401.2 (-VS), U501.2 (V-), U901.14 (VEE), U1001.2 (V-), U1002.2 (V-), U1102.2 (V-), U1202.2 (V-)
/PMOD2: J1104.10, R1201.2
/PMOD3: J1104.8, U1101.6 (IN1)
/PMOD4: J1104.6, U1101.5 (IN2)
/PMOD6: J1104.9, Q802.1 (G), R803.1
/PMOD7: J1104.7, TP601.1, U601.5
/PMOD8: J1104.5, R602.1
/PMOD_VCC: J1104.1, J1104.2
/a1_CAPN: C103.1, U101.3 (CAP-)
/a1_CAPP: C103.2, U101.6 (CAP+)
/a1_CC1: J101.A5 (CC1), R101.2
/a1_CC2: J101.B5 (CC2), R102.2
/a1_LEDG: LED102.1 (K), R104.1
/a1_LEDR: LED101.2 (A), R103.1
/a1_VBUS: F101.2, J101.A4 (VBUS), J101.A9 (VBUS), J101.B4 (VBUS), J101.B9 (VBUS)
/a2_FB: R202.1, R204.1, U201.4 (-IN)
/a2_G: Q201.1 (G), SW201.2 (B)
/a2_IN: J201.1 (In), R201.1, U201.3 (+IN)
/a2_OUT: J202.1 (In), R203.2, TP201.1
/a2_OUT_A: R202.2, R203.1, U201.1 (OUT)
/a2_VS: C202.2, Q201.3 (D), U201.5 (V+)
/a3_FB: R302.1, R304.1, U301.4 (-IN)
/a3_G: Q301.1 (G), SW301.2 (B)
/a3_IN: J301.1 (In), R301.1, U301.3 (+IN)
/a3_OUT: J302.1 (In), R303.2, TP301.1
/a3_OUT_A: R302.2, R303.1, U301.1 (OUT)
/a3_VS: C302.2, Q301.3 (D), U301.5 (V+)
/a4_FB: R402.1, R404.1, U401.4 (-IN)
/a4_G: Q401.1 (G), SW401.2 (B)
/a4_IN: J401.1 (In), R401.1, U401.3 (+IN)
/a4_OUT: J402.1 (In), R403.2, TP401.1
/a4_OUT_A: R402.2, R403.1, U401.1 (OUT)
/a4_VS: C402.2, Q401.3 (D), U401.5 (DIS), U401.6 (+VS)
/a5_FB: R502.1, R504.1, U501.4 (-IN)
/a5_G: Q501.1 (G), SW501.2 (B)
/a5_IF: C501.1, J502.2
/a5_IN: C501.2, R501.1, U501.3 (+IN)
/a5_OUT: J501.1 (In), R503.2, TP501.1
/a5_OUT_A: R502.2, R503.1, U501.1 (OUT)
/a5_VS: C503.2, J502.1, Q501.3 (D), U501.5 (V+)
/a6_G: Q601.1 (G), SW601.2 (B)
/a6_IN: J601.1 (In), R601.1
/a6_NODE: C601.1, R601.2, R602.2, U601.3 (+)
/a6_VREF: C603.1, R603.2, R604.1, U601.1 (-)
/a6_VS: C602.1, Q601.3 (D), R603.1, U601.4 (V+)
/a7_C1A: C703.2, U701.6 (C1)
/a7_C1B: C703.1, U701.7 (C2)
/a7_G: Q701.1 (G), SW701.2 (B)
/a7_IN: C701.1, J701.1 (In)
/a7_INA: C701.2, R701.1
/a7_NODE: C702.2, R702.1, U701.9 (VCOin)
/a7_OUT: J702.1 (In), R704.2
/a7_PC2: R702.2, U701.13 (PC2)
/a7_R1: R703.1, U701.11 (R1)
/a7_SIG: R701.2, U701.14 (SigIn)
/a7_VCO_A: R704.1, U701.3 (RefIn), U701.4 (FOUT)
/a7_VS: C704.1, Q701.3 (D), U701.16 (VDD)
/a8_DRN: Q802.3 (D), R802.2
/a8_G: Q801.1 (G), SW801.2 (B)
/a8_HTR: R801.1, R802.1
/a8_OUT: J801.1 (In), U801.2 (VOUT)
/a8_VS: C801.1, Q801.3 (D), R801.2, U801.1 (VDD)
/a9_BIAS: R904.1, U901.5 (BIAS)
/a9_CARA: C902.2, R908.1, U901.8 (CAR+)
/a9_CARB: R907.1, U901.10 (CAR-)
/a9_CB: C903.1, R907.2, R908.2, R909.2, R910.1
/a9_G: Q901.1 (G), SW901.2 (B)
/a9_GAIN2: R902.1, U901.2 (GAIN)
/a9_GAIN3: R902.2, U901.3 (GAIN)
/a9_IF: C905.2, J903.1 (In)
/a9_LO: C902.1, J902.1 (In)
/a9_OUTA: C905.1, R905.1, U901.6 (OUT+), U901.7 (NC)
/a9_OUTB: R906.1, U901.12 (OUT-)
/a9_RF: C901.1, J901.1 (In)
/a9_SIGA: C901.2, R901.1, U901.1 (SIG+)
/a9_SIGB: R903.1, U901.4 (SIG-)
/a9_VS: C904.1, Q901.3 (D), R905.2, R906.2, R909.1
/a10_FB: R1002.1, R1004.1, U1001.4 (-IN)
/a10_G: Q1001.1 (G), SW1001.2 (B)
/a10_IN: J1001.1 (In), R1001.1, U1001.3 (+IN)
/a10_OUT: J1002.1 (In), R1003.2
/a10_OUT_A: R1002.2, R1003.1, SW1002.1, SW1002.2, SW1002.3, SW1002.4, U1001.1 (OUT)
/a10_R1: R1005.1, SW1002.8
/a10_R2: R1006.1, SW1002.7
/a10_R3: R1007.1, SW1002.6
/a10_R4: R1008.1, SW1002.5
/a10_VS: C1002.2, C1003.1, Q1001.3 (D), U1001.5 (V+), U1002.5 (V+)
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
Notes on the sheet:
OUT
tutorial The speed of sound at 40 kHz, Warming a crystal (+-5 V)
per side (3.9 k), 1.5 k loads. Keep RF under 0.3 V and LO near 0.3 V peak (above that the carrier pair just switches,
±1.5 V
tutorial ADC samples to Python, MSK and GMSK (+-5 V)
cells (2,2), (3,2)
Gilbert cell on +-5 V: signal pair at ground (51 ohm), carrier pair at 2.5 V (51 ohm to the 10 k / 10 k bias), 1 mA
cell (2,1)
a1 power, USB-C 5 V in: +5, -5, +3.3 out
a10 impedance, V and I
tutorial The speed of sound at 40 kHz, What time is it over there? (+-5 V)
a11 ultrasound
cell (2,0)
10 k / 10 nF integrator (1.6 kHz; clock the loop at 1-10 MHz). IN takes 0 to 3.3 V, or +-1.5 V about the 1.65 V reference
USB-C power only: 5.1 k on each CC asks any source for 5 V. A 2 A PTC, a 5 V TVS (clamps at 9.2 V) and 20 uF.
±40 mV
a9 mixer, MC1496
Non-inverting OPA847 (3.9 GHz GBW at this gain, 0.85 nV/rtHz): 1 k / 10 ohm, so x101 and about 39 MHz. Its
gains above 12 (it is decompensated): do not change Rg upward. SOT-23-6, DIS tied to +VS (enabled).
The socket along the top carries +5, ground, -5, ground, +3.3: the bench's rails for a breadboard experiment.
The TMP235 reads 750 mV at 25 C and climbs 10 mV per kelvin. A feedback-control experiment: hold the TMP235 at a
Drive IN1/IN2 (Pmod IO4, IO3) in antiphase at 40 kHz for 8-20 cycles: the bridge puts 10 V peak to peak across the TX
First-order delta-sigma: the comparator decides, the FPGA registers the bit and feeds it back through 10 k into the
cell (0,1)
with a high-impedance input, not 50 ohm. No carrier-null trimmer: expect -40 dB of LO feedthrough.
Non-inverting OPA810: gain 1 + 10 k / 1.1 k = 10.1, bandwidth 140 MHz / 10 = 14 MHz. 50 ohm at the input, 49.9 ohm
in series with the output. For 40 dB out to 30 MHz use a4 (the OPA847 LNA); this tile is the FET-input, high-impedance
set point with the FPGA's PWM. (The plan's NTC divider did not fit the cell beside the two 2512s.)
DUT
EXPECT: x100 (40 dB) from 50 ohm, flat 1-30 MHz, about 3 dB noise figure from 50 ohm; keep the input under 30 mV peak
cells (2,3), (3,3)
amp with its +5 V removed draws nothing. The TPS7A2033 makes 3.3 V for the comparator and the lines that meet the FPGA.
tutorial The speed of sound at 40 kHz (+-5 V)
The LM2664 charge pump makes -5 V for the op-amp tiles (40 mA: four tiles at 10 mA); it is not switched per tile, an op
±0.3 V
its colour (p12) gives Planck's constant; a crystal (p8) shows its series and parallel resonances.
PAM8302A: 1 u couples SPEAKER IN to IN+ (IN- grounded through 1 u), the one-bit DAC on Pmod IO2 arrives through 10 k
tutorial A counter on the LEDs
cells (0,3), (1,3)
ground loops for the scope's clips, one per channel, in the board's margins

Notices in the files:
README.md:
License:
Open hardware and open source: `LICENSE` says which licence covers what (the hardware is CERN-OHL-P-2.0,
`LICENSE-HARDWARE.txt`).
hardware/amod_a.kicad_sch:
Board: Jason Gallicchio and Claude  |  open hardware, CERN-OHL-P-2.0  |  github.com/gallicchio/AMOD-and-RFMOD
